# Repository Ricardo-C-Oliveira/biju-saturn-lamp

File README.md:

# biju-saturn-lamp
Project files for Biju Saturn Lamp

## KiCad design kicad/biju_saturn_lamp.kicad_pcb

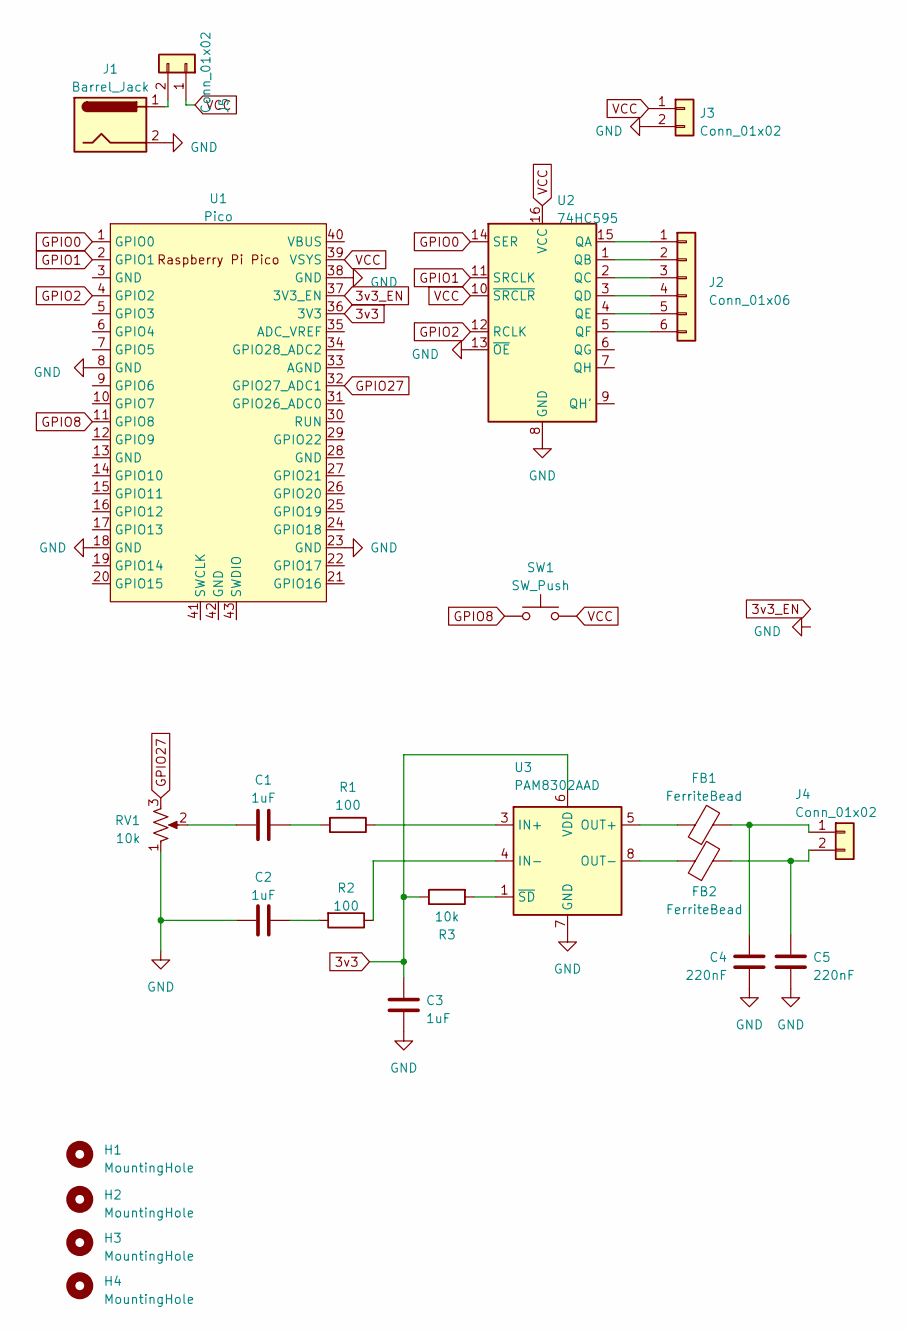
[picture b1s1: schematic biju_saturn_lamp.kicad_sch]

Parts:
C1, C2, C3: 1uF; C_0805_2012Metric_Pad1.18x1.45mm_HandSolder
C4, C5: 220nF; C_0805_2012Metric_Pad1.18x1.45mm_HandSolder
FB1, FB2: FerriteBead; R_1210_3225Metric_Pad1.30x2.65mm_HandSolder
H1, H2, H3, H4: MountingHole; MountingHole_2.2mm_M2_Pad
J1: Barrel_Jack; BarrelJack_CUI_PJ-063AH_Horizontal
J2: Conn_01x06; TerminalBlock_Phoenix_MKDS-1,5-6_1x06_P5.00mm_Horizontal
J3, J4, J5: Conn_01x02; TerminalBlock_Phoenix_MKDS-1,5-2_1x02_P5.00mm_Horizontal
R1, R2: 100; R_0805_2012Metric_Pad1.20x1.40mm_HandSolder
R3: 10k; R_0805_2012Metric_Pad1.20x1.40mm_HandSolder
RV1: 10k; Potentiometer_ACP_CA9-H3,8_Horizontal
SW1: SW_Push; TerminalBlock_Phoenix_MKDS-1,5-2_1x02_P5.00mm_Horizontal
U1: Pico; RPi_Pico_SMD_TH
U2: 74HC595; SOIC-16_3.9x9.9mm_P1.27mm
U3: PAM8302AAD; Diodes_PSOP-8

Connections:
3v3: C3.2, R3.1, U1.36 (3V3), U3.6 (VDD)
3v3_EN: U1.37 (3V3_EN)
GND: C2.1, C3.1, C4.1, C5.1, J1.2, J3.2, RV1.1, U1.8 (GND), U1.18 (GND), U1.23 (GND), U1.38 (GND), U2.8 (GND), U2.13 (~OE), U3.7 (GND)
GPIO0: U1.1 (GPIO0), U2.14 (SER)
GPIO1: U1.2 (GPIO1), U2.11 (SRCLK)
GPIO2: U1.4 (GPIO2), U2.12 (RCLK)
GPIO8: SW1.1, U1.11 (GPIO8)
GPIO27: RV1.3, U1.32 (GPIO27_ADC1)
unnamed: C1.1, RV1.2
unnamed: C1.2, R1.2
unnamed: C2.2, R2.2
unnamed: J2.1, U2.15 (QA)
unnamed: J2.2, U2.1 (QB)
unnamed: J2.3, U2.2 (QC)
unnamed: J2.4, U2.3 (QD)
unnamed: J2.5, U2.4 (QE)
unnamed: J2.6, U2.5 (QF)
unnamed: C4.2, FB1.2, J4.1
unnamed: C5.2, FB2.2, J4.2
unnamed: J1.1, J5.2
unnamed: R1.1, U3.3 (IN+)
unnamed: R2.1, U3.4 (IN-)
unnamed: FB1.1, U3.5 (OUT+)
unnamed: FB2.1, U3.8 (OUT-)
unnamed: R3.2, U3.1 (~SD)
VCC: J3.1, J5.1, SW1.2, U1.39 (VSYS), U2.10 (~SRCLR), U2.16 (VCC)

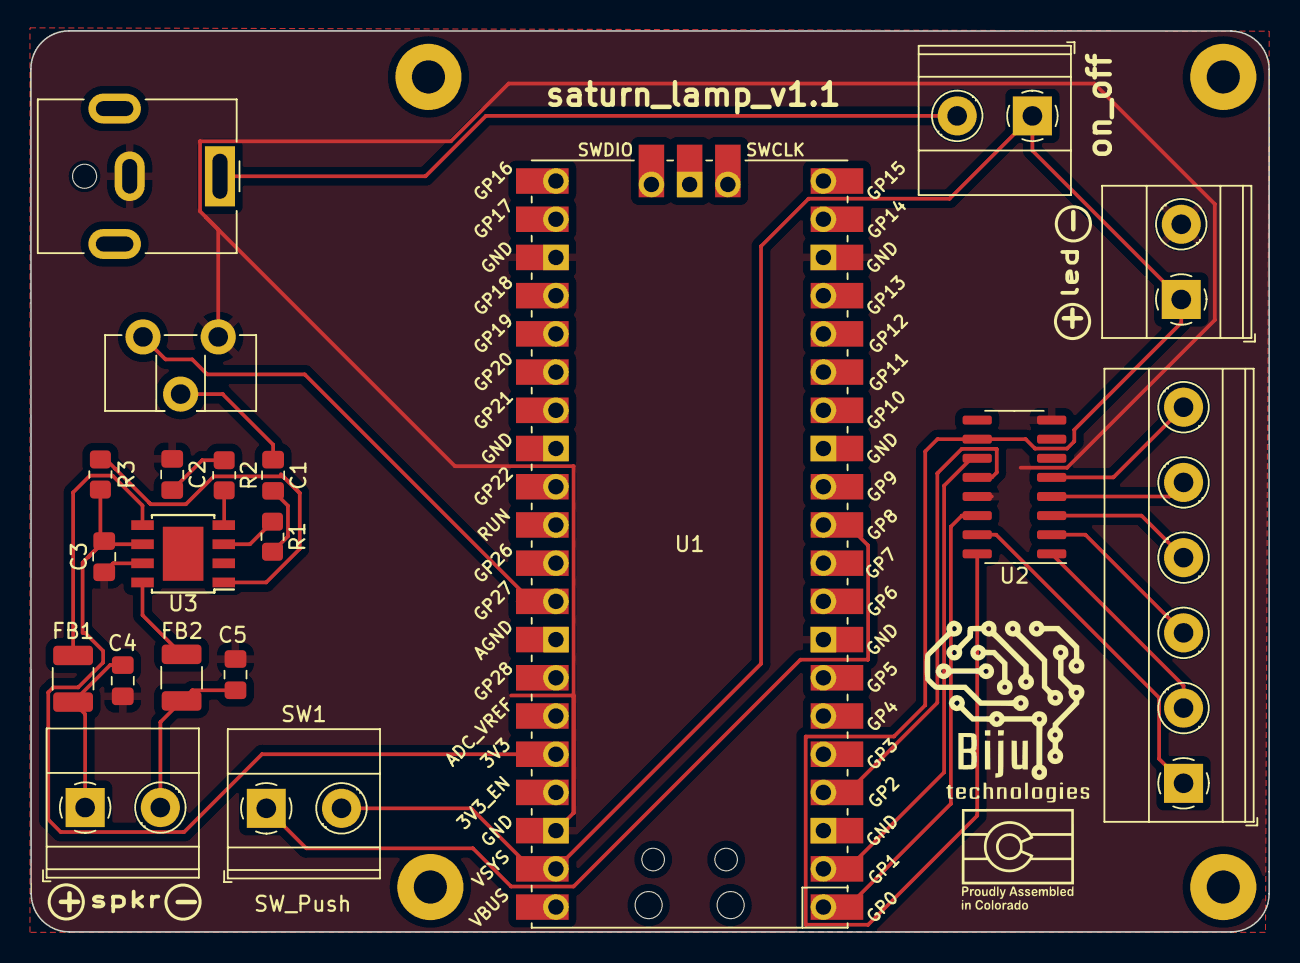
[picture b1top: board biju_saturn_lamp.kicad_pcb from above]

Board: 2 copper layers, 82.3 x 59.9 mm, 24 parts (0 on the bottom side), 25 nets.

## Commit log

2024-01-27 add DS_Store to gitignore
2024-01-27 update pcb
2024-01-28 add logo to pcb
2024-01-29 fix on-off switch
2024-02-11 add base stl
2024-03-09 add base theo stl
